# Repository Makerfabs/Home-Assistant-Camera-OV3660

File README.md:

# Makerfabs Home Assistant Camera OV3660

## Intruduce

[Product Link](https://www.makerfabs.com/ov3660-3m-camera-for-home-assistant.html)

[Wiki Link]()

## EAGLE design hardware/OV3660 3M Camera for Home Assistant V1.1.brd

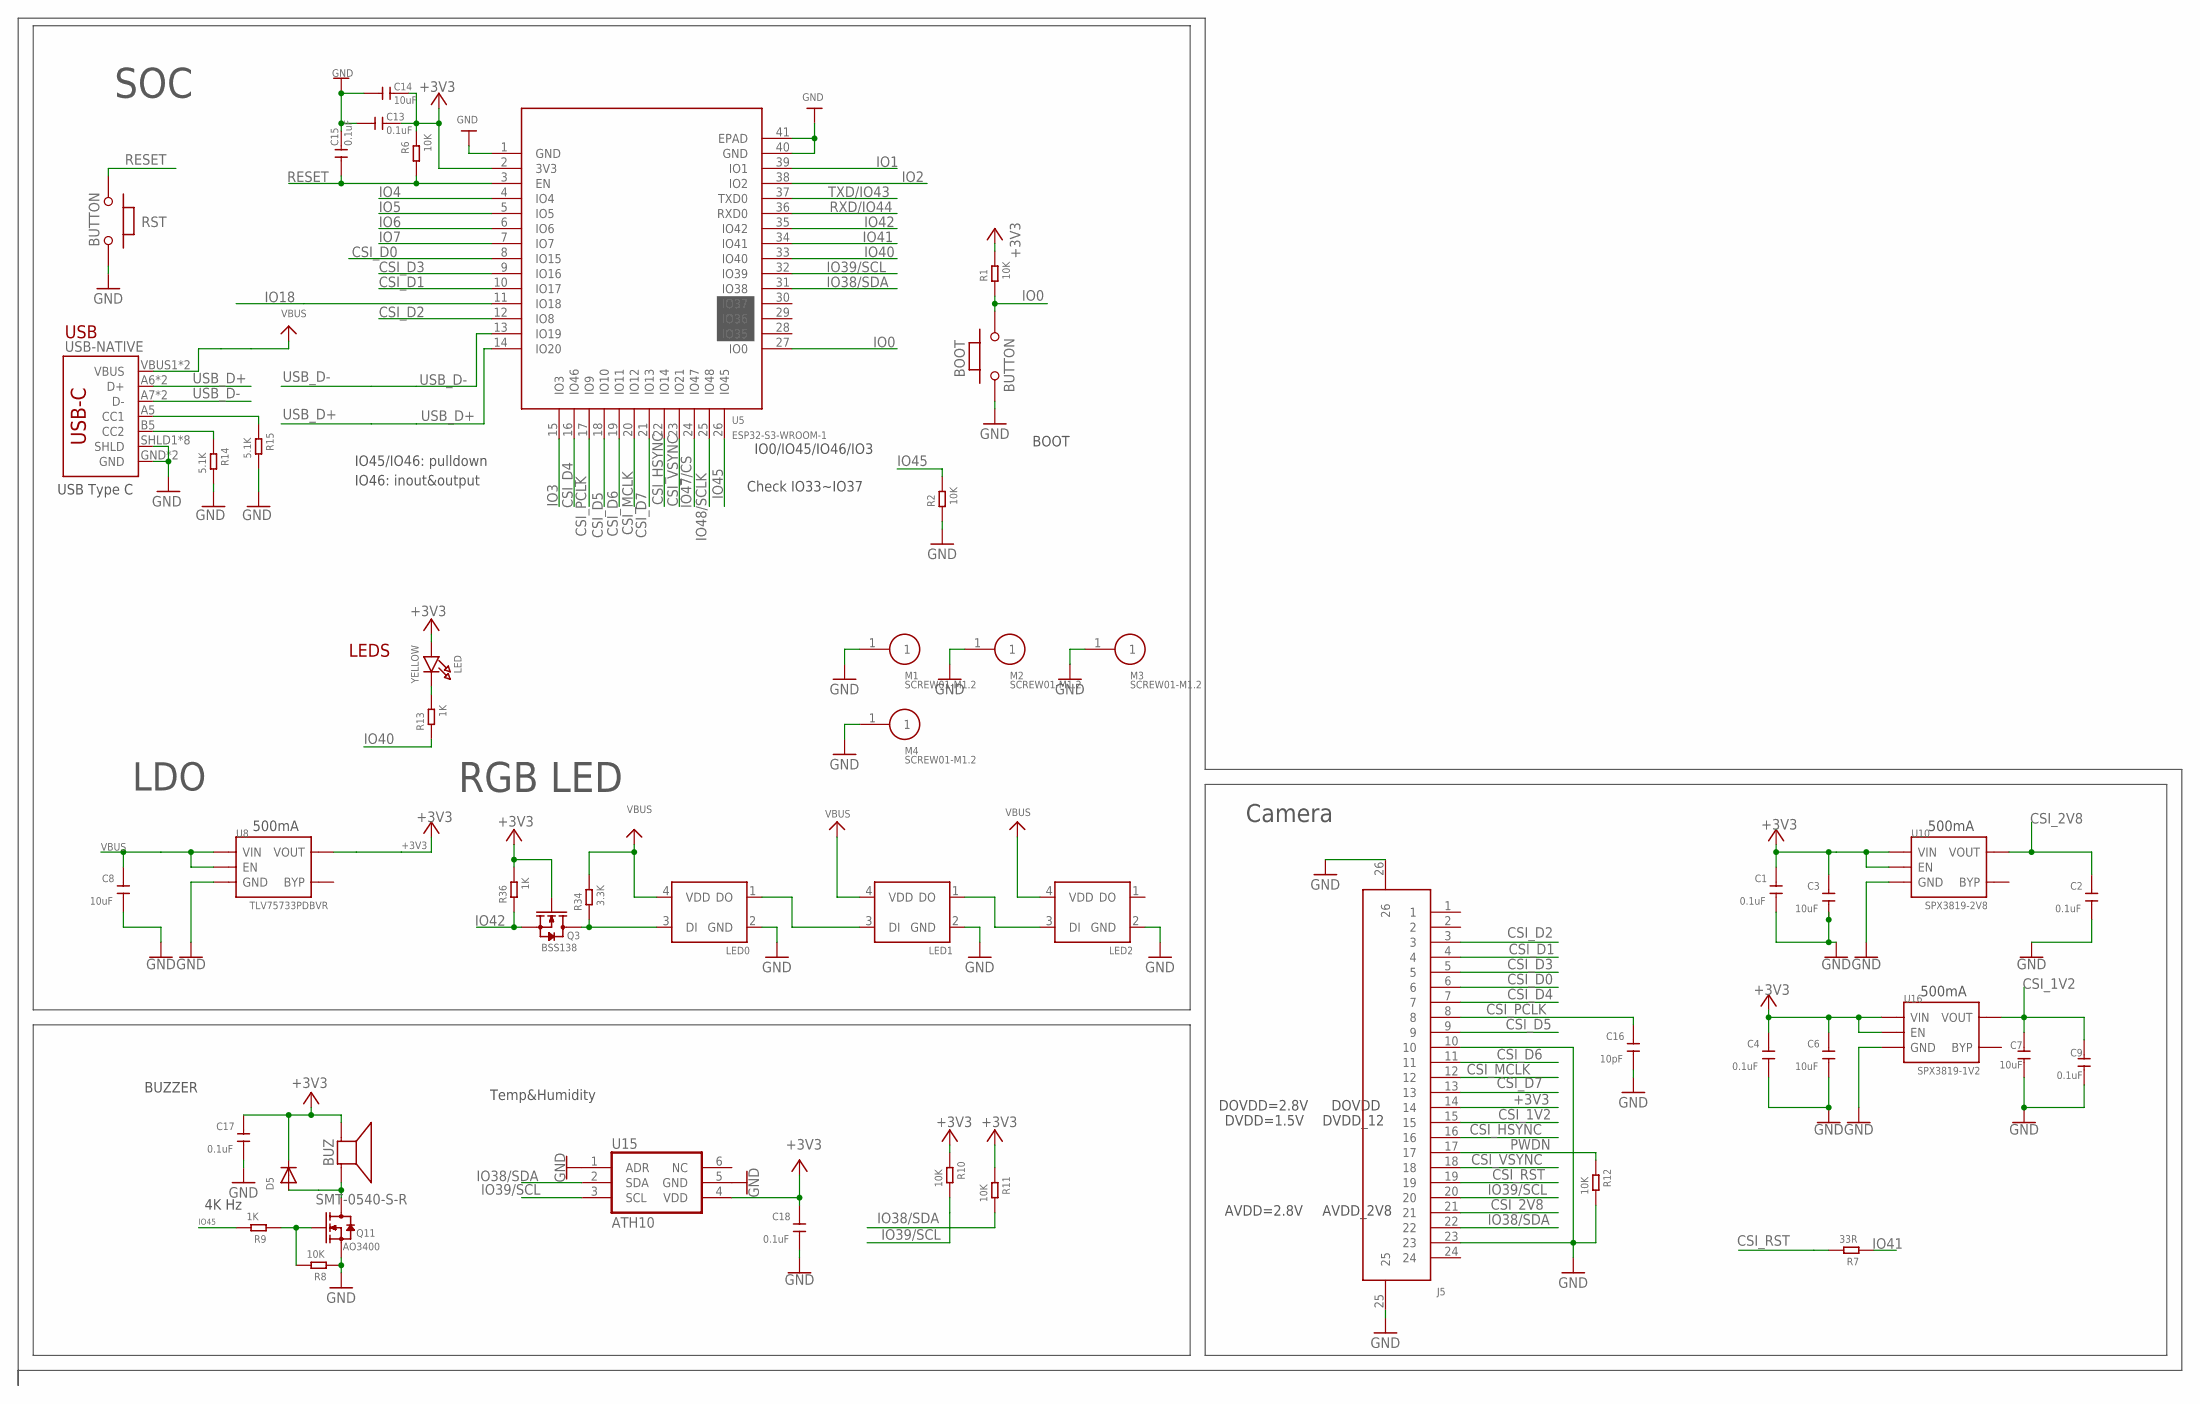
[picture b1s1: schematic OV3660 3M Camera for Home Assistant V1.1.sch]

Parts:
BOOT: BUTTON; 157SW
BUZ: SMT-0540-S-R
C1, C2, C4, C9, C13, C15, C17, C18: 0.1uF; DISCRETE_C0402
C3, C6, C7, C8, C14: 10uF; DISCRETE_C0402
C16: 10pF; DISCRETE_C0402
D5: DIODESOD-323F; SOD-323F
J5: FPC-24P; SMD26-50P-1760L450W
LED: YELLOW; CHIPLED_0805_NOOUTLINE
LED0, LED1, LED2: WS2812B-2020
M1, M2, M3, M4: SCREW01-M1.2; THD1-M1.2
Q3: BSS138; SOT23@1
Q11: AO3400; SOT23@1
R1, R2, R6, R8, R10, R11, R12: 10K; DISCRETE_R0402
R7: 33R; DISCRETE_R0402
R9, R13, R36: 1K; DISCRETE_R0402
R14, R15: 5.1K; DISCRETE_R0402
R34: 3.3K; DISCRETE_R0402
RST: BUTTON; 157SW
U5: ESP32-S3-WROOM-1
U8: TLV75733PDBVR; SOT23-5
U10: SPX3819-2V8; SOT23-5
U15: ATH10; AHT10
U16: SPX3819-1V2; SOT23-5
USB-NATIVE: USB_C5; USB-C-16P-5

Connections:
+3V3: BUZ.+ (-), C1.2, C3.2, C4.2, C6.2, C13.1, C14.1, C17.2, C18.2, D5.C, J5.14, LED.A, Q3.1 (G), R1.2, R6.2, R10.1, R11.1, R36.2, U5.2 (3V3), U8.5 (VOUT), U10.1 (VIN), U10.3 (EN), U15.4 (VDD), U16.1 (VIN), U16.3 (EN)
CSI_1V2: C7.2, C9.2, J5.15, U16.5 (VOUT)
CSI_2V8: C2.2, J5.21, U10.5 (VOUT)
CSI_D0: J5.6, U5.8 (IO15)
CSI_D1: J5.4, U5.10 (IO17)
CSI_D2: J5.3, U5.12 (IO8)
CSI_D3: J5.5, U5.9 (IO16)
CSI_D4: J5.7, U5.16 (IO46)
CSI_D5: J5.9, U5.18 (IO10)
CSI_D6: J5.11, U5.19 (IO11)
CSI_D7: J5.13, U5.21 (IO13)
CSI_HSYNC: J5.16, U5.22 (IO14)
CSI_MCLK: J5.12, U5.20 (IO12)
CSI_PCLK: C16.2, J5.8, U5.17 (IO9)
CSI_RST: J5.19, R7.2
CSI_VSYNC: J5.18, U5.23 (IO21)
GND: BOOT.1, C1.1, C2.1, C3.1, C4.1, C6.1, C7.1, C8.1, C9.1, C13.2, C14.2, C15.1, C16.1, C17.1, C18.1, J5.10, J5.23, J5.25, J5.26, LED0.2 (GND), LED1.2 (GND), LED2.2 (GND), M1.1, M2.1, M3.1, M4.1, Q11.2 (S), R2.1, R8.1, R12.2, R14.2, R15.2, RST.1, U5.1 (GND), U5.40 (GND), U5.41 (EPAD), U8.2 (GND), U10.2 (GND), U15.1 (ADR), U15.5 (GND), U16.2 (GND), USB-NATIVE.GND, USB-NATIVE.GND2 (GND), USB-NATIVE.SHLD1 (SHLD), USB-NATIVE.SHLD2 (SHLD), USB-NATIVE.SHLD3 (SHLD), USB-NATIVE.SHLD4 (SHLD), USB-NATIVE.SHLD5 (SHLD), USB-NATIVE.SHLD6 (SHLD), USB-NATIVE.SHLD7 (SHLD), USB-NATIVE.SHLD8 (SHLD)
IO0: BOOT.2, R1.1, U5.27 (IO0)
IO1: U5.39 (IO1)
IO2: U5.38 (IO2)
IO3: U5.15 (IO3)
IO4: U5.4 (IO4)
IO5: U5.5 (IO5)
IO6: U5.6 (IO6)
IO7: U5.7 (IO7)
IO18: U5.11 (IO18)
IO38/SDA: J5.22, R11.2, U5.31 (IO38), U15.2 (SDA)
IO39/SCL: J5.20, R10.2, U5.32 (IO39), U15.3 (SCL)
IO40: R13.1, U5.33 (IO40)
IO41: R7.1, U5.34 (IO41)
IO42: Q3.2 (S), R36.1, U5.35 (IO42)
IO45: R2.2, R9.2, U5.26 (IO45)
IO47/CS: U5.24 (IO47)
IO48/SCLK: U5.25 (IO48)
M-1: BUZ.- (+), D5.A, Q11.3 (D)
unnamed: LED1.1 (DO), LED2.3 (DI)
unnamed: LED0.1 (DO), LED1.3 (DI)
unnamed: LED.C, R13.2
unnamed: LED0.3 (DI), Q3.3 (D), R34.1
unnamed: Q11.1 (G), R8.2, R9.1
unnamed: R15.1, USB-NATIVE.A5 (CC1)
unnamed: R14.1, USB-NATIVE.B5 (CC2)
PWDN: J5.17, R12.1
RESET: C15.2, R6.1, RST.2, U5.3 (EN)
RXD/IO44: U5.36 (RXD0)
TXD/IO43: U5.37 (TXD0)
USB_D+: U5.14 (IO20), USB-NATIVE.A6 (D+), USB-NATIVE.B6 (D+)
USB_D-: U5.13 (IO19), USB-NATIVE.A7 (D-), USB-NATIVE.B7 (D-)
VBUS: C8.2, LED0.4 (VDD), LED1.4 (VDD), LED2.4 (VDD), R34.2, U8.1 (VIN), U8.3 (EN), USB-NATIVE.VBUS1 (VBUS), USB-NATIVE.VBUS2 (VBUS)

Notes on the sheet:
500mA
LDO
LEDS
BOOT
IO45/IO46: pulldown
IO46: inout&output
USB
USB Type C
IO0/IO45/IO46/IO3
Check IO33~IO37
SOC
DVDD=1.5V
AVDD=2.8V
DOVDD=2.8V
Camera
AVDD_2V8
DVDD_12
DOVDD
BUZZER
4K Hz
Temp&Humidity
RGB LED

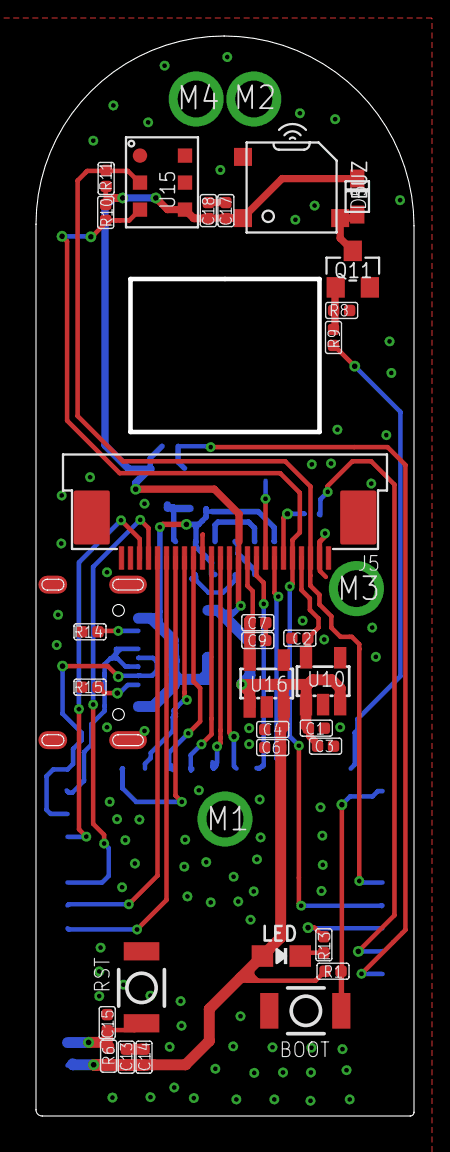
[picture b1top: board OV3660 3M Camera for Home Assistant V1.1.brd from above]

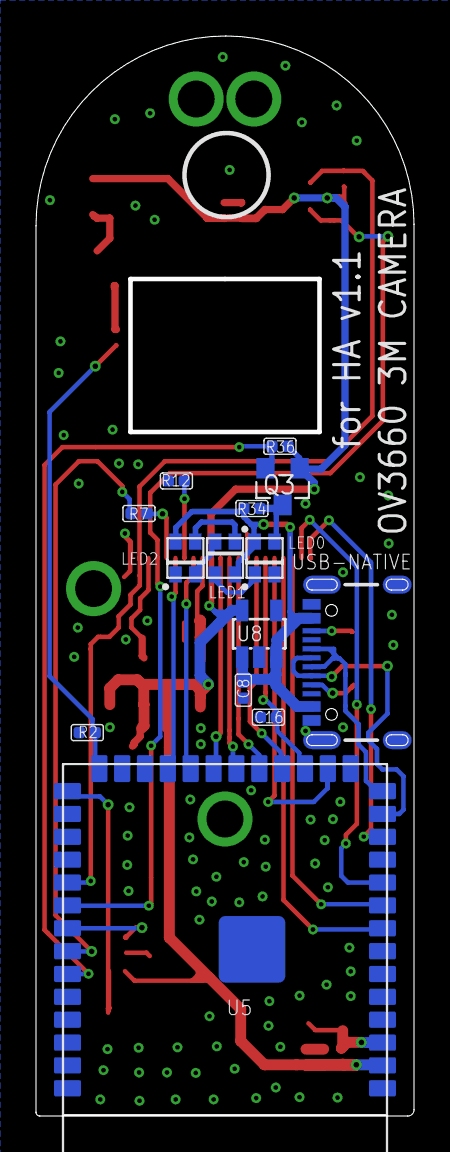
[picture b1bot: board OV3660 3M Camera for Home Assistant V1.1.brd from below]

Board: 2 copper layers, 20.7 x 59.7 mm, 49 parts (14 on the bottom side), 37 nets.

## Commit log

2026-01-03 add camera ov3660
2026-01-19 fix yaml&delete gerber.rar
2026-01-19 fix yaml
2026-01-19 update hardware
2026-06-18 Update ha-camera.yaml
    Commented out temp sensor, since it is not installed form factory.

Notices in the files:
parts and their libraries:
microbuilder: This work is placed in the public domain, and may be freely used for commercial and non-commercial work with the following conditions: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
SparkFun-PowerSymbols: Licensing: Creative Commons ShareAlike 4.0 International - https://creativecommons.org/licenses/by-sa/4.0
